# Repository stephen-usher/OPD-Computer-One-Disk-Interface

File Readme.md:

# The recreated Computer One floppy disk interface for the ICL One Per Desk.
## Version 1.0: 14th July, 2024.

This is a reverse engineered version of the Computer One floppy disk interface for the ICL One Per Desk.

The circuitry has been simpified by replacing a great deal of discrete logic with a single GAL to handle the address decoding and the clock circuit has been replaced by a crystal oscillator.

The included ROM image also has beenmodified to add a BIOS Parameter Block to the boot sector on the floppy disk format so that MSDOS PCs and Atari STs can read it. Unfortunately if PCs try to write to the disk it will corrupt the format. In tests Atari STs can correctly write to the disks.

It should be noted that using the OPD Microdrive Utilities copy is hit and miss with Gotek drives for some reason. With real floppy disks it's fine.

If you wish to use EPROMs larger than a 27C128 use bodge wires to connect pins 1 and 27 of the ROM to ground or put multiple copies of the image onto the EPROM.

What you will need:

7 x 10nF 0805 ceramic capacitors (decoupling on rear).

1 x Right-angled 2.54mm pitch 15x2 header socket (female).

1 x 2.54mm pitch through hole 17x2 shrounded header.

2 x 74LS06

1 x 74LS245

1 x 74LS175

1 x 27C128 EPROM (or larger pin compatible EPROM or EEPROM)

1 x WD1772

1 x Microchip ATF16V8B GAL

1 x 8MHz crystal oscillator

1 x 100uF 16V radial electrolytic capacitor

1 x 47uF 16V radial electrolytic capacitor

1 x 9 pin 1K matrix resistor

1 x 10K 2W resistor

1 x 10 ohm 2W resistor

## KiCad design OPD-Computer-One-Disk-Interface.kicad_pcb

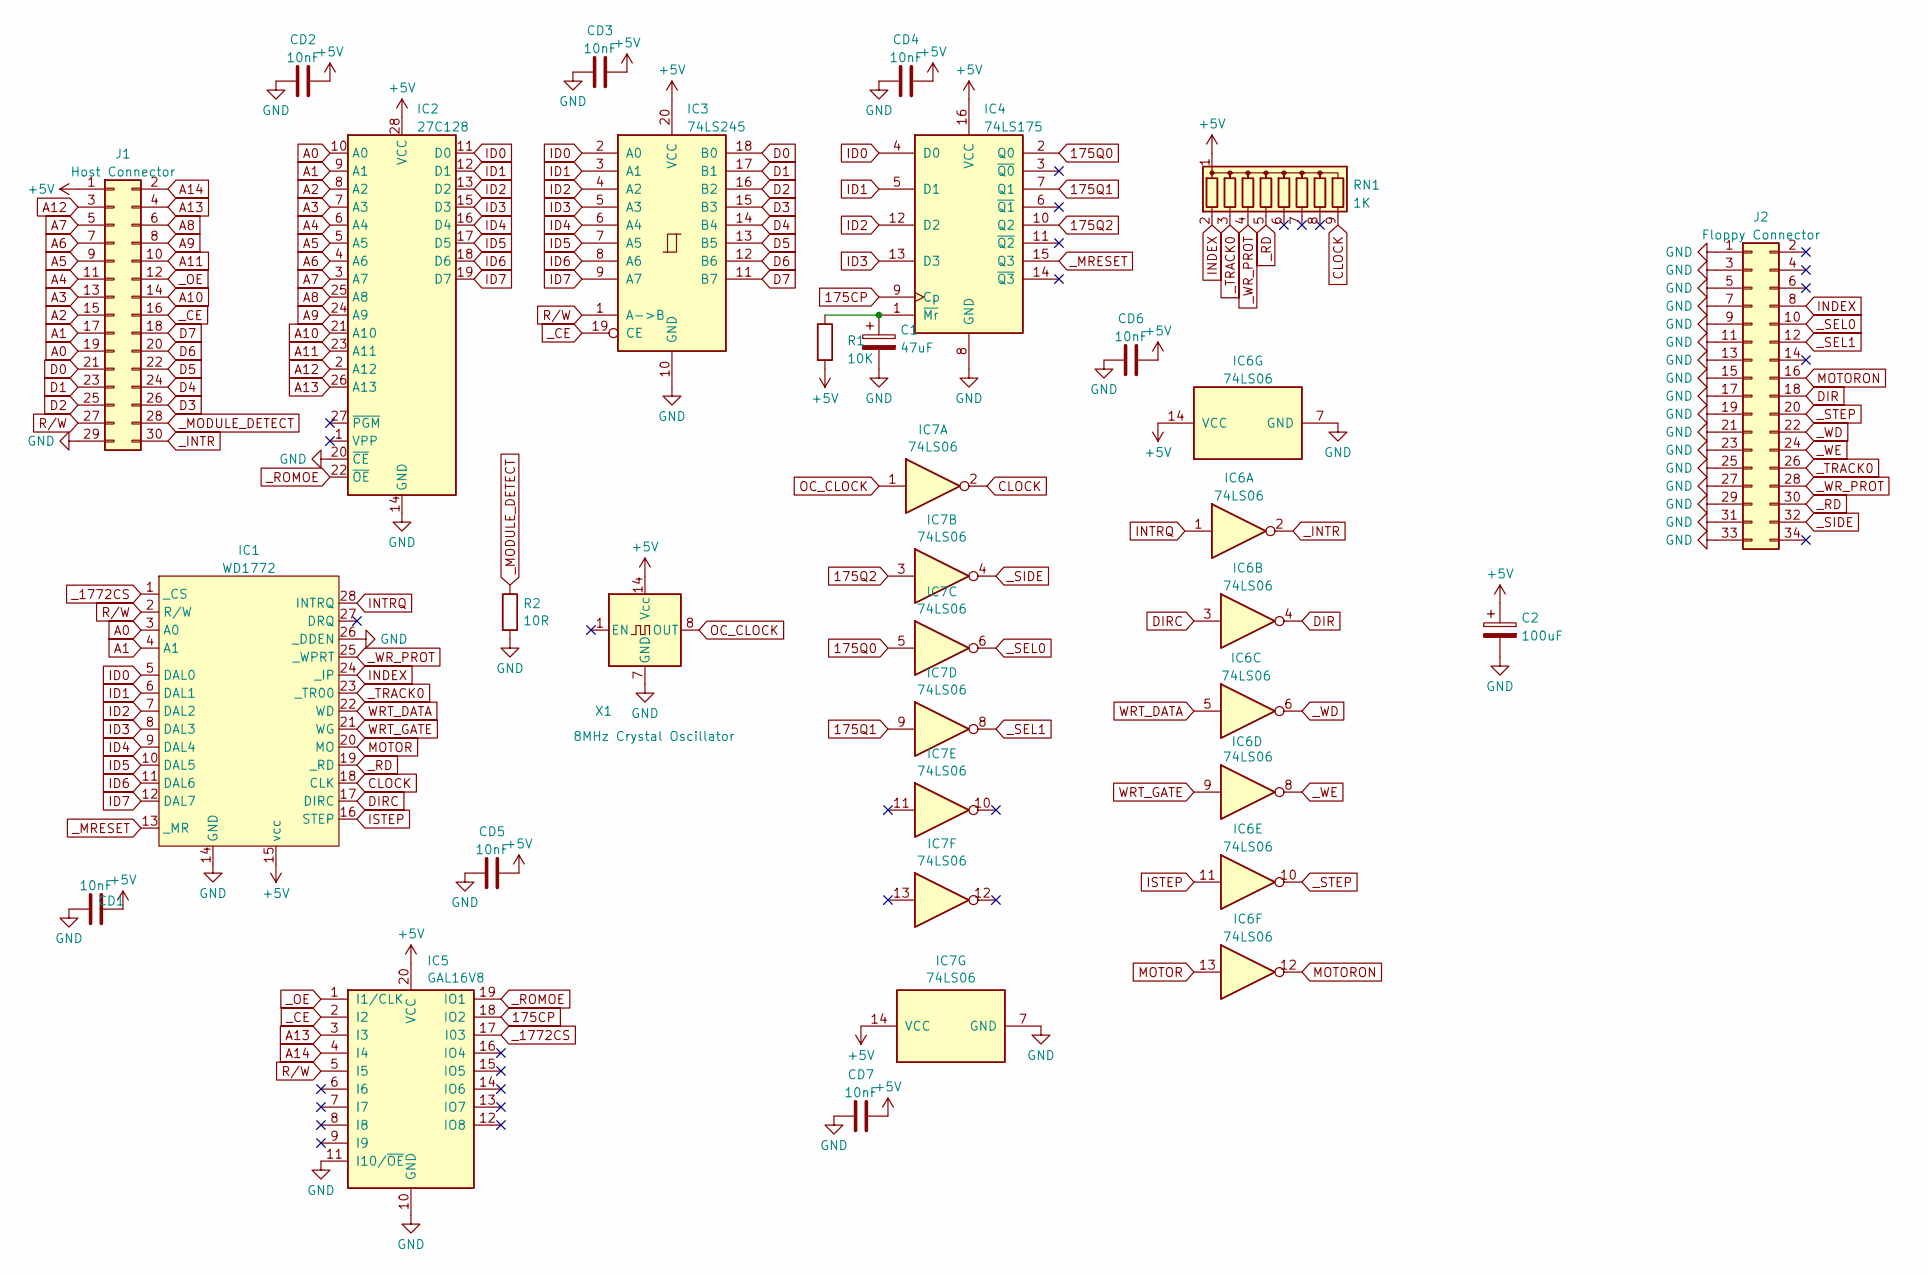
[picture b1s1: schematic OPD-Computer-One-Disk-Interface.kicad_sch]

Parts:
C1: 47uF; CP_Radial_D8.0mm_P3.80mm
C2: 100uF; CP_Radial_D8.0mm_P5.00mm
CD1, CD2, CD3, CD4, CD5, CD6, CD7: 10nF; C_0805_2012Metric_Pad1.18x1.45mm_HandSolder
IC1: WD1772; DIP-28_W15.24mm
IC2: 27C128; DIP-28_W15.24mm
IC3: 74LS245; DIP-20_W7.62mm
IC4: 74LS175; DIP-16_W7.62mm
IC5: GAL16V8; DIP-20_W7.62mm
IC6, IC7: 74LS06; DIP-14_W7.62mm
J1: Host Connector; PinSocket_2x15_P2.54mm_Horizontal
J2: Floppy Connector; PinHeader_2x17_P2.54mm_Vertical
R1: 10K; R_Axial_DIN0207_L6.3mm_D2.5mm_P10.16mm_Horizontal
R2: 10R; R_Axial_DIN0207_L6.3mm_D2.5mm_P10.16mm_Horizontal
RN1: 1K; R_Array_SIP9
X1: 8MHz Crystal Oscillator; Oscillator_DIP-14

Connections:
175CP: IC4.9 (Cp), IC5.18 (IO2)
175Q0: IC4.2 (Q0), IC7.5
175Q1: IC4.7 (Q1), IC7.9
175Q2: IC4.10 (Q2), IC7.3
+5V: C2.1, CD1.1, CD2.1, CD3.1, CD4.1, CD5.1, CD6.1, CD7.1, IC1.15 (vcc), IC2.28 (VCC), IC3.20 (VCC), IC4.16 (VCC), IC5.20 (VCC), IC6.14 (VCC), IC7.14 (VCC), J1.1, R1.2, RN1.1 (common), X1.14 (Vcc)
A0: IC1.3 (A0), IC2.10 (A0), J1.19
A1: IC1.4 (A1), IC2.9 (A1), J1.17
A2: IC2.8 (A2), J1.15
A3: IC2.7 (A3), J1.13
A4: IC2.6 (A4), J1.11
A5: IC2.5 (A5), J1.9
A6: IC2.4 (A6), J1.7
A7: IC2.3 (A7), J1.5
A8: IC2.25 (A8), J1.6
A9: IC2.24 (A9), J1.8
A10: IC2.21 (A10), J1.14
A11: IC2.23 (A11), J1.10
A12: IC2.2 (A12), J1.3
A13: IC2.26 (A13), IC5.3 (I3), J1.4
A14: IC5.4 (I4), J1.2
CLOCK: IC1.18 (CLK), IC7.2, RN1.9 (R8)
D0: IC3.18 (B0), J1.21
D1: IC3.17 (B1), J1.23
D2: IC3.16 (B2), J1.25
D3: IC3.15 (B3), J1.26
D4: IC3.14 (B4), J1.24
D5: IC3.13 (B5), J1.22
D6: IC3.12 (B6), J1.20
D7: IC3.11 (B7), J1.18
DIR: IC6.4, J2.18
DIRC: IC1.17 (DIRC), IC6.3
GND: C1.2, C2.2, CD1.2, CD2.2, CD3.2, CD4.2, CD5.2, CD6.2, CD7.2, IC1.14 (GND), IC1.26 (_DDEN), IC2.14 (GND), IC2.20 (~CE), IC3.10 (GND), IC4.8 (GND), IC5.10 (GND), IC5.11 (I10/~OE), IC6.7 (GND), IC7.7 (GND), J1.29, J2.1, J2.3, J2.5, J2.7, J2.9, J2.11, J2.13, J2.15, J2.17, J2.19, J2.21, J2.23, J2.25, J2.27, J2.29, J2.31, J2.33, R2.2, X1.7 (GND)
ID0: IC1.5 (DAL0), IC2.11 (D0), IC3.2 (A0), IC4.4 (D0)
ID1: IC1.6 (DAL1), IC2.12 (D1), IC3.3 (A1), IC4.5 (D1)
ID2: IC1.7 (DAL2), IC2.13 (D2), IC3.4 (A2), IC4.12 (D2)
ID3: IC1.8 (DAL3), IC2.15 (D3), IC3.5 (A3), IC4.13 (D3)
ID4: IC1.9 (DAL4), IC2.16 (D4), IC3.6 (A4)
ID5: IC1.10 (DAL5), IC2.17 (D5), IC3.7 (A5)
ID6: IC1.11 (DAL6), IC2.18 (D6), IC3.8 (A6)
ID7: IC1.12 (DAL7), IC2.19 (D7), IC3.9 (A7)
INDEX: IC1.24 (_IP), J2.8, RN1.2 (R1)
INTRQ: IC1.28 (INTRQ), IC6.1
ISTEP: IC1.16 (STEP), IC6.11
MOTOR: IC1.20 (MO), IC6.13
MOTORON: IC6.12, J2.16
unnamed: C1.1, IC4.1 (~Mr), R1.1
OC_CLOCK: IC7.1, X1.8 (OUT)
R/W: IC1.2 (R/W), IC3.1 (A->B), IC5.5 (I5), J1.27
WRT_DATA: IC1.22 (WD), IC6.5
WRT_GATE: IC1.21 (WG), IC6.9
_1772CS: IC1.1 (_CS), IC5.17 (I03)
_CE: IC3.19 (CE), IC5.2 (I2), J1.16
_INTR: IC6.2, J1.30
_MODULE_DETECT: J1.28, R2.1
_MRESET: IC1.13 (_MR), IC4.15 (Q3)
_OE: IC5.1 (I1/CLK), J1.12
_RD: IC1.19 (_RD), J2.30, RN1.5 (R4)
_ROMOE: IC2.22 (~OE), IC5.19 (IO1)
_SEL0: IC7.6, J2.10
_SEL1: IC7.8, J2.12
_SIDE: IC7.4, J2.32
_STEP: IC6.10, J2.20
_TRACK0: IC1.23 (_TR00), J2.26, RN1.3 (R2)
_WD: IC6.6, J2.22
_WE: IC6.8, J2.24
_WR_PROT: IC1.25 (_WPRT), J2.28, RN1.4 (R3)

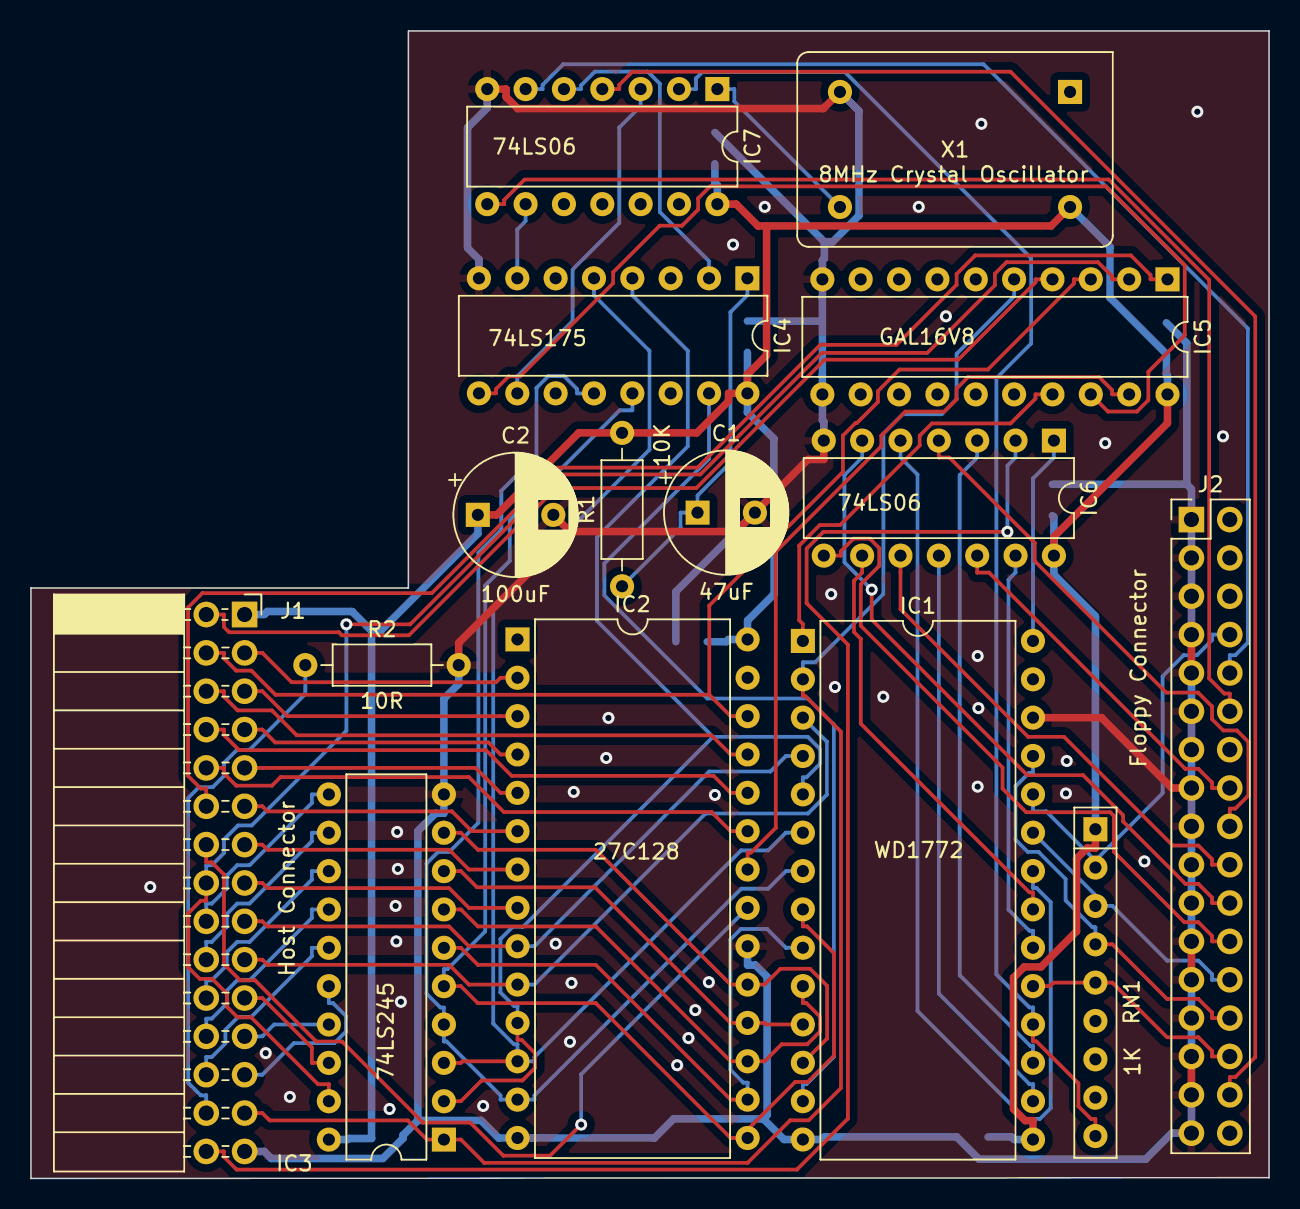
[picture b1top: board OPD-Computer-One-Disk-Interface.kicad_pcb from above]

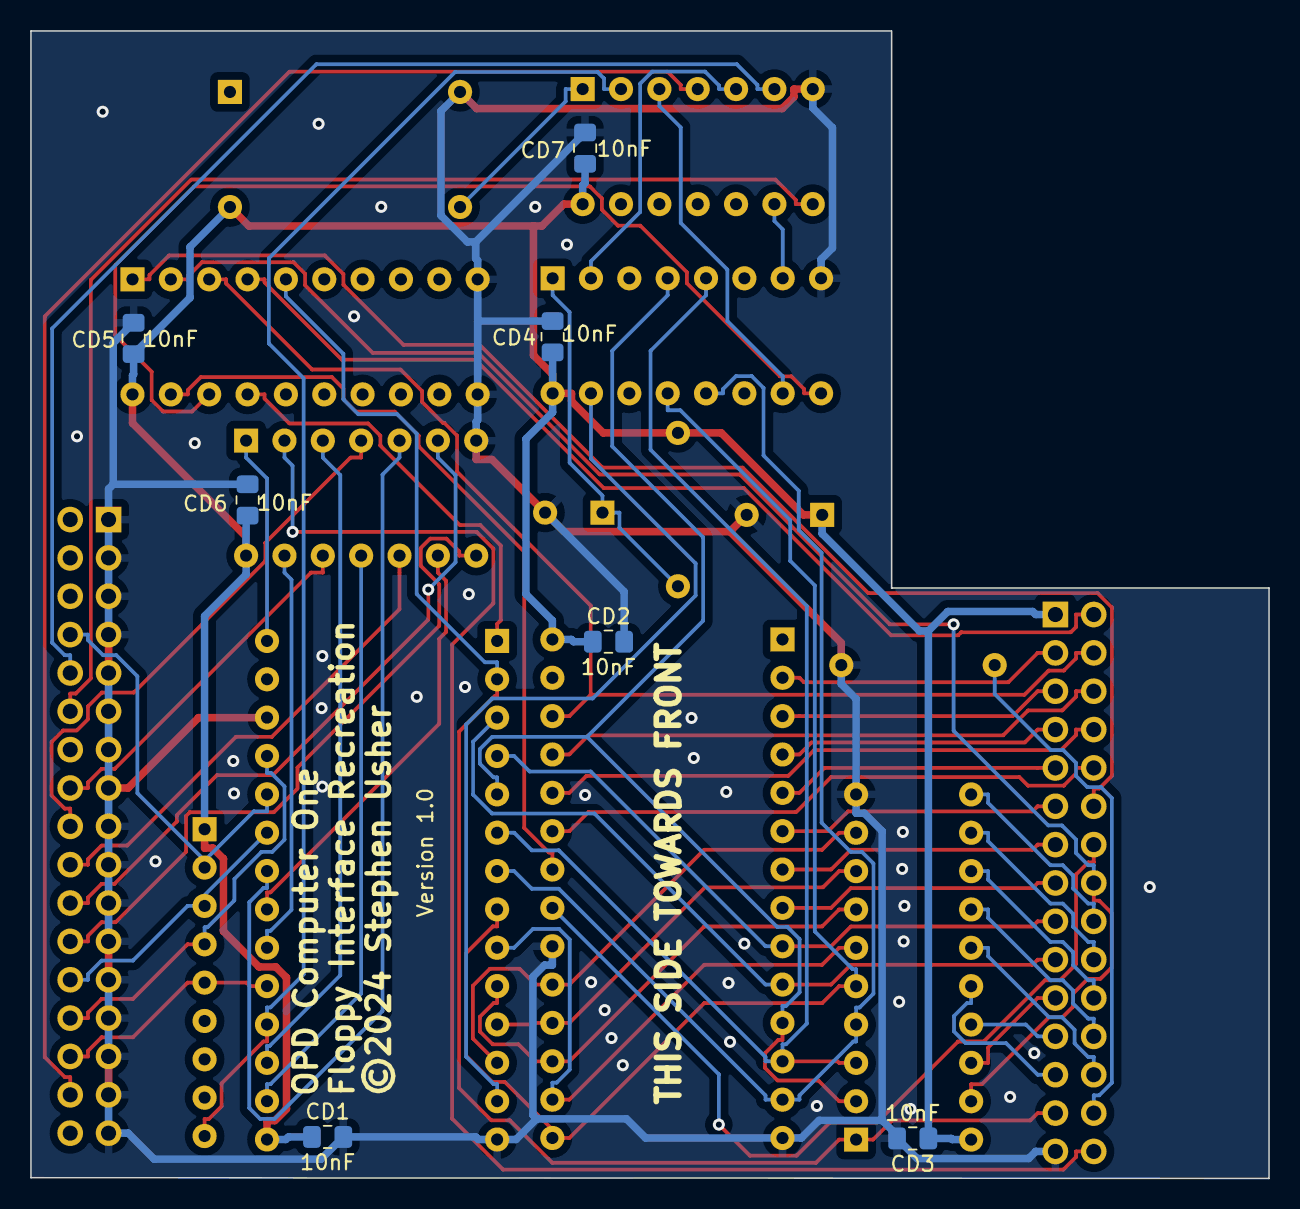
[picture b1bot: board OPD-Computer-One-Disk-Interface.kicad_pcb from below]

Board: 2 copper layers, 82.0 x 76.0 mm, 22 parts (7 on the bottom side), 66 nets.

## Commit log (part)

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2024-07-15 Fixed typo in copyright date on rear silkscreen.
2024-07-17 Added a 3D printed case.

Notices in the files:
OPD-Computer-One-Disk-Interface.kicad_pcb:
©2024 Stephen Usher
